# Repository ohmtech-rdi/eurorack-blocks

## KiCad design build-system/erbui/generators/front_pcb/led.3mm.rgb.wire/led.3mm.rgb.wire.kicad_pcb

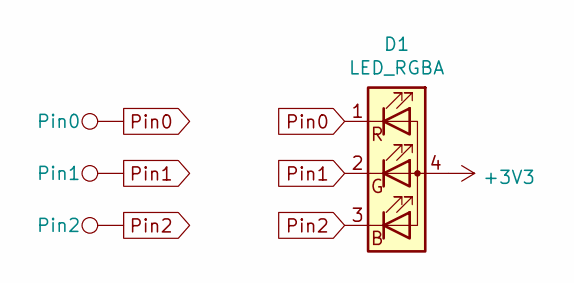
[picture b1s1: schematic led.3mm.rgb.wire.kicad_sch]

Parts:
D1: LED_RGBA; LED_Cree-PLCC4_3.2x2.8mm_CCW
Pin0, Pin1, Pin2: TestPoint; TestPoint_Pad_D1.5mm

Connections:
+3V3: D1.4 (A)
Pin0: D1.1 (RK), Pin0.1
Pin1: D1.2 (GK), Pin1.1
Pin2: D1.3 (BK), Pin2.1

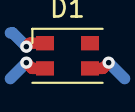
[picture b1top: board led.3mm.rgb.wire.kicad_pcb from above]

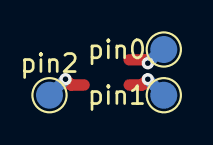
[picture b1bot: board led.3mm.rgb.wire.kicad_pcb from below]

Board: 2 copper layers, 4 parts (3 on the bottom side), 3 nets.
